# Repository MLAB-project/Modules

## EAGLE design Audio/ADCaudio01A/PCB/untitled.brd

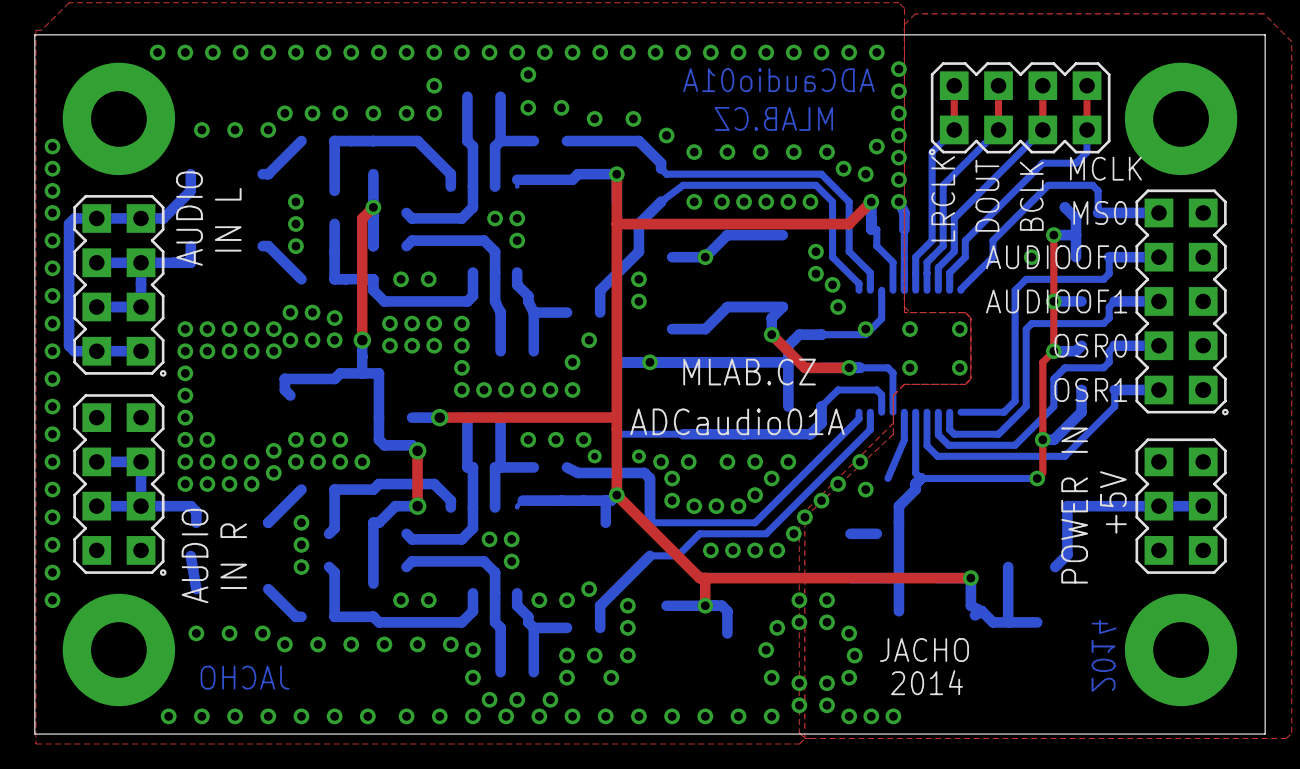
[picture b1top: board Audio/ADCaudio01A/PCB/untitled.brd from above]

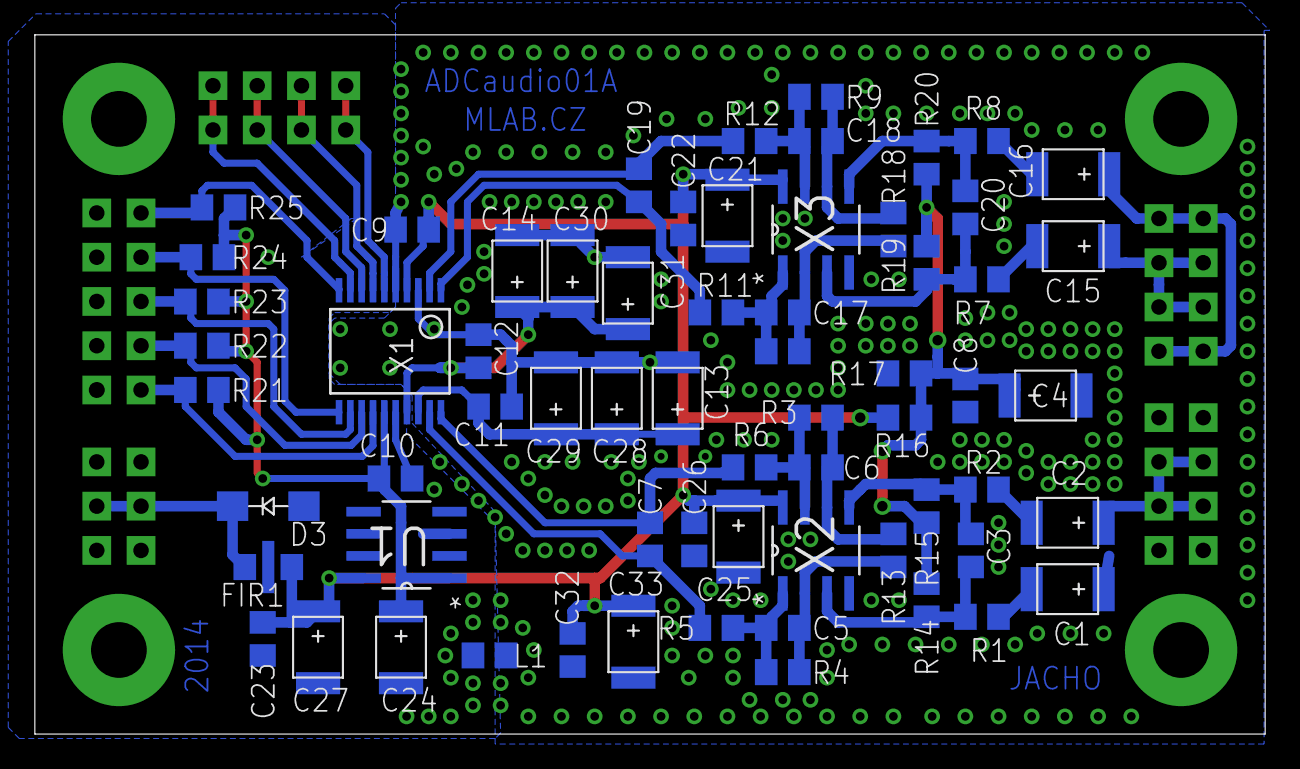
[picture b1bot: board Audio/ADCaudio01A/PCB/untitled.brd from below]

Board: 2 copper layers, 70.6 x 40.1 mm, 74 parts (65 on the bottom side), 39 nets.

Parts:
C1, C2, C4, C13, C14, C15, C16, C24, C28, C29, C30, C31: 10uF; B
C3, C7, C19, C20: 4n7; C0805
C5, C6, C17, C18: 180pF; C0805
C8, C11, C12, C22, C23, C26, C32: 100nF; C0805
C9, C10: 4u7; C0805
C21, C25, C27, C33: 47uF; B
D3: M4; SMA
FIR1: F0805
L1: L0805
R1, R2, R3, R4, R7, R8, R9, R10, R13, R14, R15, R16, R17, R18, R19, R20: 1k; 0805
R5, R6, R11, R12, R21, R22, R23, R24, R25: 22R; 0805
SV1: MA05-2
SV2, SV3, SV5: MA04-2
SV4: MA03-2
U1: LE33CD-TR; SOIC127P600X175-8N
X1: WM8786; SSOP20
X2, X3: LT6231CS; SO8
X4, X5, X6, X7: SROUB3M

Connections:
1: C20.1, R7.2, R19.1, X3.3
4: C3.1, R1.2, R14.1, X2.3
+3.3V: C10.2, C24.+, R21.2, R22.2, R23.2, R24.2, R25.2, U1.1, X1.15
+5V: C9.1, C21.+, C22.1, C23.1, C25.+, C26.1, C27.+, C32.1, C33.+, FIR1.3, R16.2, U1.8, X1.4, X2.8, X3.8
AGND: C1.+, C4.-, C8.2, C9.2, C11.1, C12.1, C13.-, C14.-, C16.+, C21.-, C22.2, C25.-, C26.2, C28.-, C29.-, C30.-, C31.-, C32.2, C33.-, L1.2, R17.1, SV3.1, SV3.2, SV3.7, SV3.8, SV5.1, SV5.2, SV5.7, SV5.8, X1.3, X1.5, X2.4, X3.4
AUDIOOF0: R24.1, SV1.8, X1.11
AUDIOOF1: R23.1, SV1.6, X1.12
AVDD/2: C4.+, C8.1, R14.2, R15.2, R16.1, R17.2, R19.2, R20.2
BCLK: SV2.5, SV2.6, X1.8
DGND: C10.1, C23.2, C24.-, C27.-, D3.A, FIR1.2, L1.1, SV1.1, SV1.3, SV1.5, SV1.7, SV1.9, SV4.1, SV4.2, SV4.5, SV4.6, U1.2, U1.3, U1.5, U1.6, U1.7, X1.16, X6.P$1, X7.P$1
DOUT: SV2.3, SV2.4, X1.7
LRCLK: SV2.1, SV2.2, X1.6
MCLK: SV2.7, SV2.8, X1.9
MS0: R25.1, SV1.10, X1.10
unnamed: C5.2, R4.1, R13.2, X2.2
unnamed: C1.-, R1.1
unnamed: C6.2, R3.1, R13.1, X2.6
unnamed: C2.-, R2.1
unnamed: C6.1, R3.2, R6.1, X2.7
unnamed: C7.1, R5.2, X1.19
unnamed: C17.2, R10.1, R18.2, X3.2
unnamed: C15.-, R7.1
unnamed: C18.2, R9.1, R18.1, X3.6
unnamed: C16.-, R8.1
unnamed: C18.1, R9.2, R12.1, X3.7
unnamed: C19.1, R11.2, X1.1
unnamed: C15.+, SV5.3, SV5.4, SV5.5, SV5.6
unnamed: C20.2, R8.2, R20.1, X3.5
unnamed: C2.+, SV3.3, SV3.4, SV3.5, SV3.6
unnamed: C19.2, R12.2, X1.2
unnamed: C12.2, C14.+, C30.+, C31.+, X1.17
unnamed: C11.2, C13.+, C28.+, C29.+, X1.18
unnamed: C3.2, R2.2, R15.1, X2.5
unnamed: C5.1, R4.2, R5.1, X2.1
unnamed: C17.1, R10.2, R11.1, X3.1
unnamed: C7.2, R6.2, X1.20
unnamed: D3.K, FIR1.1, SV4.3, SV4.4
OSR0: R22.1, SV1.4, X1.13
OSR1: R21.1, SV1.2, X1.14

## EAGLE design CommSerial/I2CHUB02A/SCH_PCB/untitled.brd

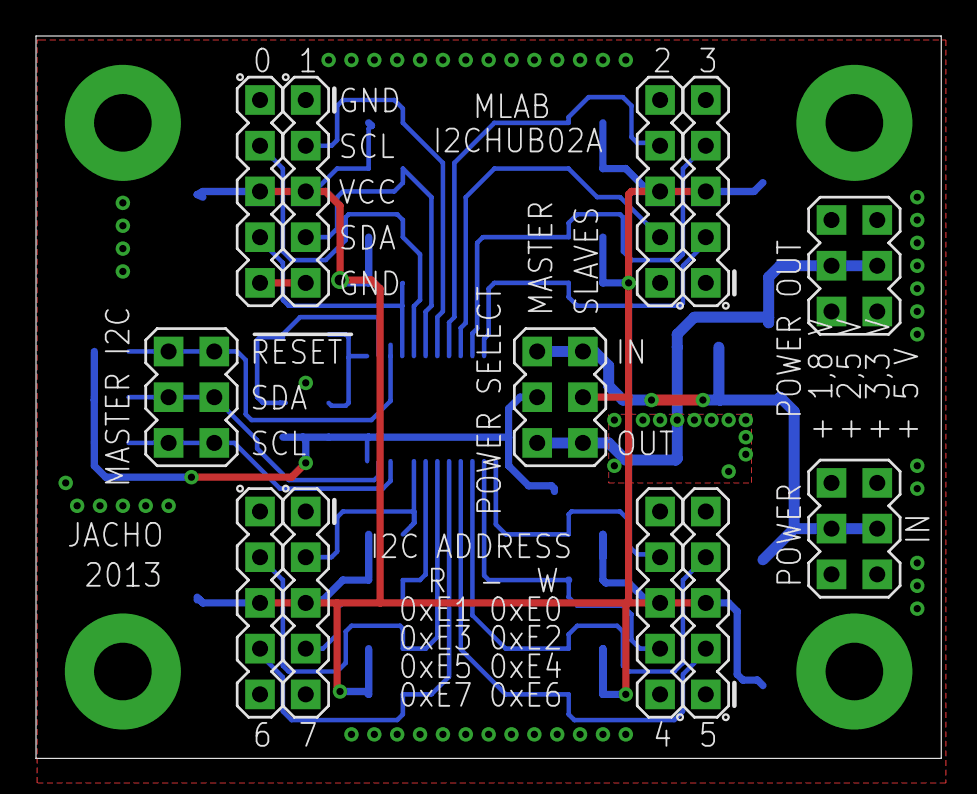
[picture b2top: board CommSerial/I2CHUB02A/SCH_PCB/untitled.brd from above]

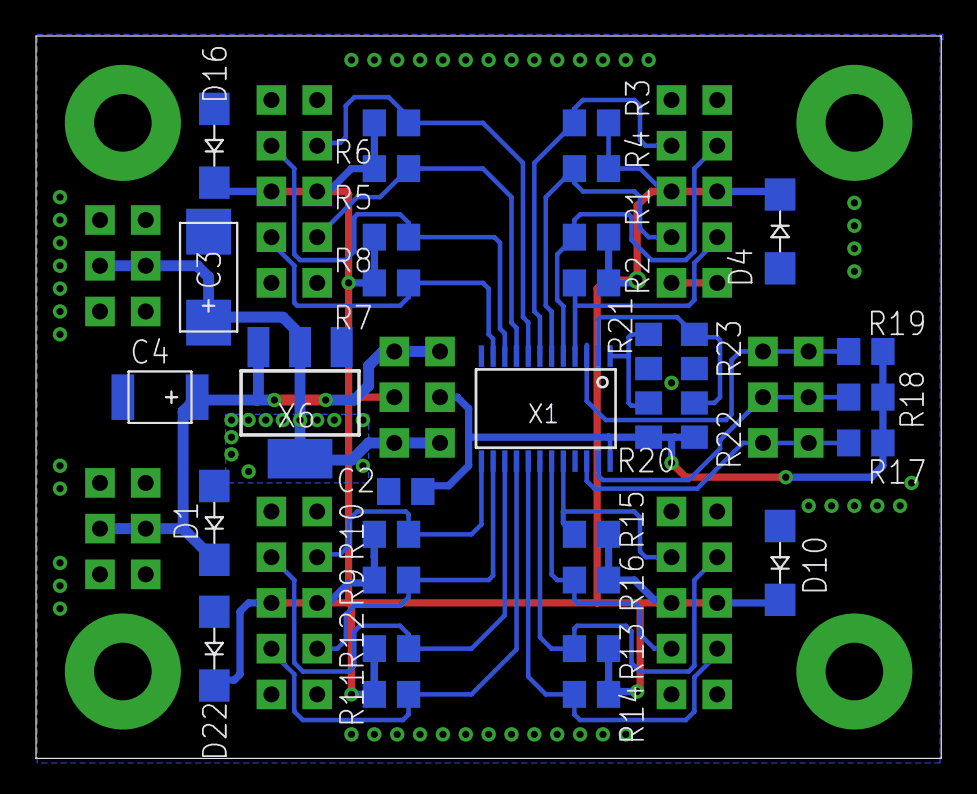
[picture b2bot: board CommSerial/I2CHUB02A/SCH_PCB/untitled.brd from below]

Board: 2 copper layers, 50.3 x 40.1 mm, 49 parts (33 on the bottom side), 26 nets.

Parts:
C2: 100nF; C0805
C3: 47uF; C
C4: 10uF; B
D1: SMA
D4, D10, D16, D22: TRANSIL; SMA
R1, R2, R17, R18, R19: 4k7; 0805
R3, R4, R5, R6, R7, R8, R9, R10, R11, R12, R13, R14, R15, R16: 0805
R20, R21, R22, R23: 0R; 0805
SV1, SV2, SV3, SV4, SV5, SV6, SV7, SV8: MA05-1
SV9, SV10, SV11: MA03-2
SW1: MA03-2
X1: TSS0P24
X2, X3, X4, X5: SROUB3M
X6: LM1117-3.3; SOT223

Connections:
+3.3V: C3.+, SV11.3, SV11.4, SW1.5, SW1.6, X6.2, X6.4
+V1: D4.K, D10.K, D16.K, D22.K, R1.2, R2.2, R3.2, R4.2, R5.2, R6.2, R7.2, R8.2, R9.2, R10.2, R11.2, R12.2, R13.2, R14.2, R15.2, R16.2, SV1.3, SV2.3, SV3.3, SV4.3, SV5.3, SV6.3, SV7.3, SV8.3, SW1.4
+VCC: C4.+, D1.K, SV10.3, SV10.4, SW1.1, SW1.2, X6.3
/RESET: R19.1, SV9.5, SV9.6, X1.3
GND: C2.2, C3.-, C4.-, D1.A, D4.A, D10.A, D16.A, D22.A, R21.1, R23.1, SV1.1, SV1.5, SV2.1, SV2.5, SV3.1, SV3.5, SV4.1, SV4.5, SV5.1, SV5.5, SV6.1, SV6.5, SV7.1, SV7.5, SV8.1, SV8.5, SV10.1, SV10.2, SV10.5, SV10.6, SV11.1, SV11.2, SV11.5, SV11.6, X1.12, X1.21, X2.P$1, X3.P$1, X4.P$1, X5.P$1, X6.1
unnamed: C2.1, R17.2, R18.2, R19.2, R20.2, R22.2, SW1.3, X1.24
unnamed: R20.1, R21.2, X1.1
unnamed: R22.1, R23.2, X1.2
SC0: R1.1, SV1.2, X1.5
SC1: R3.1, SV2.2, X1.7
SC2: R5.1, SV3.2, X1.9
SC3: R7.1, SV4.2, X1.11
SC4: R9.1, SV5.2, X1.14
SC5: R11.1, SV6.2, X1.16
SC6: R13.1, SV7.2, X1.18
SC7: R15.1, SV8.2, X1.20
SCL: R17.1, SV9.1, SV9.2, X1.22
SD0: R2.1, SV1.4, X1.4
SD1: R4.1, SV2.4, X1.6
SD2: R6.1, SV3.4, X1.8
SD3: R8.1, SV4.4, X1.10
SD4: R10.1, SV5.4, X1.13
SD5: R12.1, SV6.4, X1.15
SD6: R14.1, SV7.4, X1.17
SD7: R16.1, SV8.4, X1.19
SDA: R18.1, SV9.3, SV9.4, X1.23

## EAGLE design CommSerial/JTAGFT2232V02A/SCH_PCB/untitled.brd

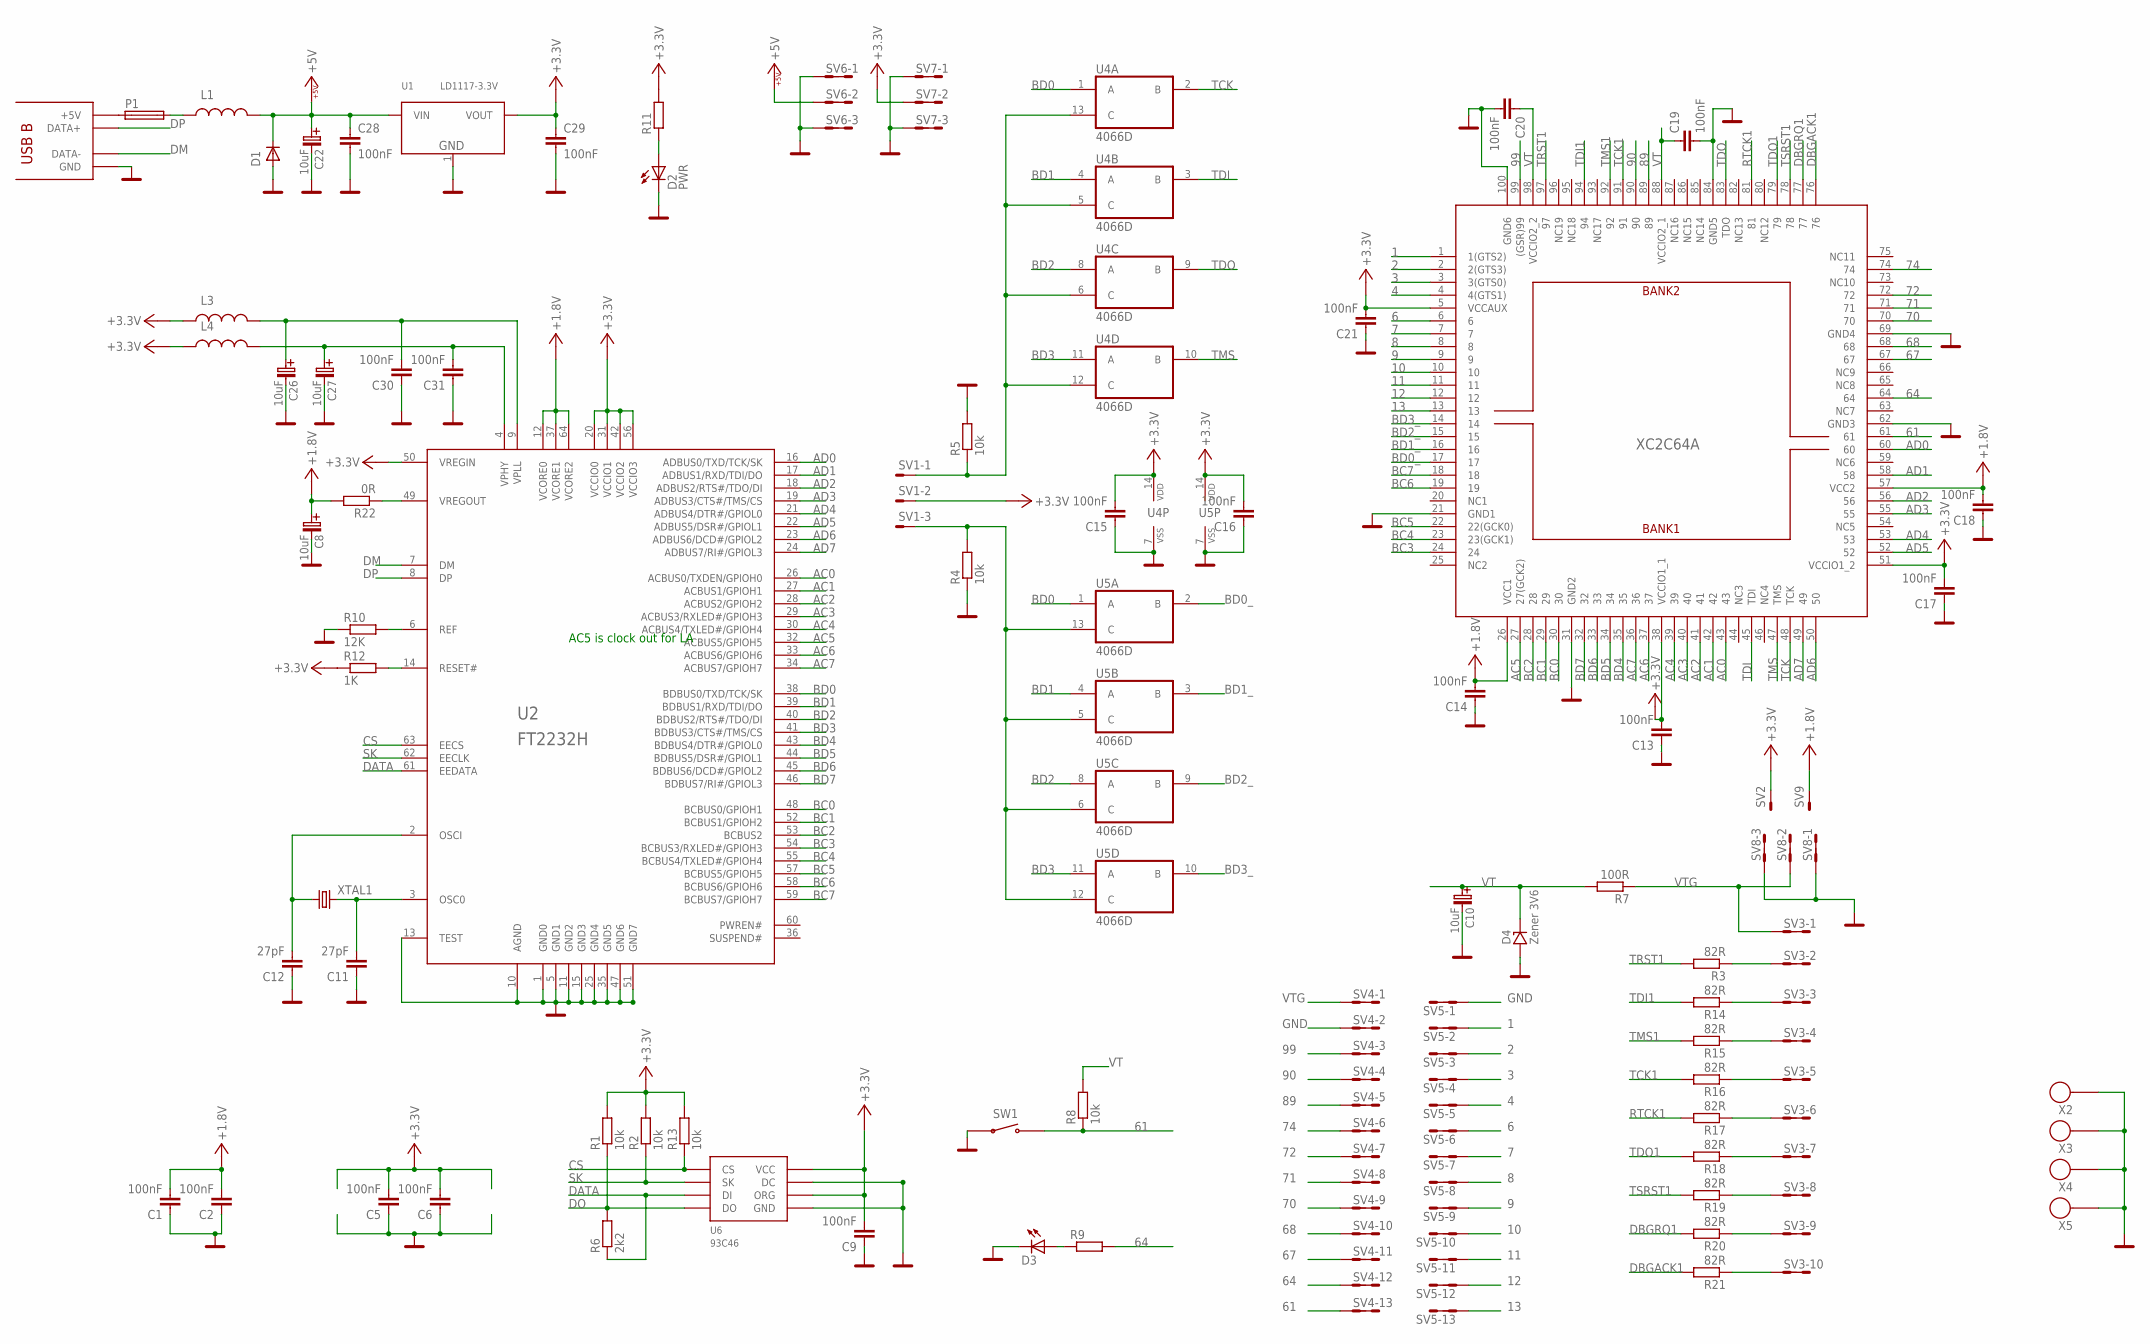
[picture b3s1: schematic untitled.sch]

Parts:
C1, C2, C5, C6, C9, C13, C14, C15, C16, C17, C18, C19, C20, C21, C28, C29, C30, C31: 100nF; C0805
C8, C10, C22, C26, C27: 10uF; B
C11, C12: 27pF; C0805
D1: D-OB.SMA; SMA
D2: PWR; 1206
D3: LED1206; 1206
D4: Zener 3V6; MINIMELF
L1: L0805
L3, L4: L1210; 1210
P1: POJISTKA_1812; 1812
R1, R2, R4, R5, R8, R13: 10k; 0805
R3, R14, R15, R16, R17, R18, R19, R20, R21: 82R; 0805
R6: 2k2; 0805
R7: 100R; 0805
R9, R11: R0805; 0805
R10: 12K; 0805
R12: 1K; 0805
R22: 0R; 0805
SV1: MA03-1
SV2, SV9: MA01-1
SV3: MA10-2
SV4, SV5: MA13-2
SV6, SV7, SV8: MA03-2
SW1: TACT-64K
U1: LD1117-3.3V; SOT223
U2: FT2232H; LQFP64
U3: XC2C64A; VQ100
U4, U5: 4066D; SO14
U6: 93C46; SOIC8
X1: USB_B
X2, X3, X4, X5: SROUB3M
XTAL1: KRYSLAL_S49; S49

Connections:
1: SV5.3, SV5.4, U3.1 (1(GTS2))
2: SV5.5, SV5.6, U3.2 (2(GTS3))
3: SV5.7, SV5.8, U3.3 (3(GTS0))
4: SV5.9, SV5.10, U3.4 (4(GTS1))
6: SV5.11, SV5.12, U3.6
7: SV5.13, SV5.14, U3.7
8: SV5.15, SV5.16, U3.8
9: SV5.17, SV5.18, U3.9
10: SV5.19, SV5.20, U3.10
11: SV5.21, SV5.22, U3.11
12: SV5.23, SV5.24, U3.12
13: SV5.25, SV5.26, U3.13
61: R8.1, SV4.25, SV4.26, SW1.P$3, SW1.P$4, U3.61
64: R9.2, SV4.23, SV4.24, U3.64
67: SV4.21, SV4.22, U3.67
68: SV4.19, SV4.20, U3.68
70: SV4.17, SV4.18, U3.70
71: SV4.15, SV4.16, U3.71
72: SV4.13, SV4.14, U3.72
74: SV4.11, SV4.12, U3.74
89: SV4.9, SV4.10, U3.89
90: SV4.7, SV4.8, U3.90
99: SV4.5, SV4.6, U3.99 ((GSR)99)
+1.8V: C1.2, C2.2, C8.+ (C_EL+), C14.2, C18.2, R22.2, SV9.1, U2.12 (VCORE0), U2.37 (VCORE1), U2.64 (VCORE2), U3.26 (VCC1), U3.57 (VCC2)
+3.3V: C5.2, C6.2, C9.2, C13.2, C15.2, C16.2, C17.2, C21.2, C29.1, L3.P$1 (1), L4.P$1 (1), R1.2, R2.2, R11.2, R12.1, R13.2, SV1.2, SV2.1, SV7.3, SV7.4, U1.2 (VOUT), U2.20 (VCCIO0), U2.31 (VCCIO1), U2.42 (VCCIO2), U2.50 (VREGIN), U2.56 (VCCIO3), U3.5 (VCCAUX), U3.38 (VCCIO1_1), U3.51 (VCCIO1_2), U4.14 (VDD), U5.14 (VDD), U6.6 (ORG), U6.8 (VCC)
+5V: C22.+ (C_EL+), C28.1, D1.K (C), L1.2, SV6.3, SV6.4, U1.3 (VIN)
AC0: U2.26 (ACBUS0/TXDEN/GPIOH0), U3.43
AC1: U2.27 (ACBUS1/GPIOH1), U3.42
AC2: U2.28 (ACBUS2/GPIOH2), U3.41
AC3: U2.29 (ACBUS3/RXLED#/GPIOH3), U3.40
AC4: U2.30 (ACBUS4/TXLED#/GPIOH4), U3.39
AC5: U2.32 (ACBUS5/GPIOH5), U3.27 (27(GCK2))
AC6: U2.33 (ACBUS6/GPIOH6), U3.37
AC7: U2.34 (ACBUS7/GPIOH7), U3.36
AD0: U2.16 (ADBUS0/TXD/TCK/SK), U3.60
AD1: U2.17 (ADBUS1/RXD/TDI/DO), U3.58
AD2: U2.18 (ADBUS2/RTS#/TDO/DI), U3.56
AD3: U2.19 (ADBUS3/CTS#/TMS/CS), U3.55
AD4: U2.21 (ADBUS4/DTR#/GPIOL0), U3.53
AD5: U2.22 (ADBUS5/DSR#/GPIOL1), U3.52
AD6: U2.23 (ADBUS6/DCD#/GPIOL2), U3.50
AD7: U2.24 (ADBUS7/RI#/GPIOL3), U3.49
BC0: U2.48 (BCBUS0/GPIOH1), U3.30
BC1: U2.52 (BCBUS1/GPIOH2), U3.29
BC2: U2.53 (BCBUS2), U3.28
BC3: U2.54 (BCBUS3/RXLED#/GPIOH3), U3.24
BC4: U2.55 (BCBUS4/TXLED#/GPIOH4), U3.23 (23(GCK1))
BC5: U2.57 (BCBUS5/GPIOH5), U3.22 (22(GCK0))
BC6: U2.58 (BCBUS6/GPIOH6), U3.19
BC7: U2.59 (BCBUS7/GPIOH7), U3.18
BD0: U2.38 (BDBUS0/TXD/TCK/SK), U4.1 (A), U5.1 (A)
BD0_: U3.17, U5.2 (B)
BD1: U2.39 (BDBUS1/RXD/TDI/DO), U4.4 (A), U5.4 (A)
BD1_: U3.16, U5.3 (B)
BD2: U2.40 (BDBUS2/RTS#/TDO/DI), U4.8 (A), U5.8 (A)
BD2_: U3.15, U5.9 (B)
BD3: U2.41 (BDBUS3/CTS#/TMS/CS), U4.11 (A), U5.11 (A)
BD3_: U3.14, U5.10 (B)
BD4: U2.43 (BDBUS4/DTR#/GPIOL0), U3.35
BD5: U2.44 (BDBUS5/DSR#/GPIOL1), U3.34
BD6: U2.45 (BDBUS6/DCD#/GPIOL2), U3.33
BD7: U2.46 (BDBUS7/RI#/GPIOL3), U3.32
CS: R13.1, U2.63 (EECS), U6.1 (CS)
DATA: R6.1, U2.61 (EEDATA), U6.3 (DI)
DBGACK1: R21.2, U3.76
DBGRQ1: R20.2, U3.77
DM: U2.7 (DM), X1.2 (DATA-)
DO: R1.1, R6.2, U6.4 (DO)
DP: U2.8 (DP), X1.3 (DATA+)
GND: C1.1, C2.1, C5.1, C6.1, C8.- (C_EL-), C9.1, C10.- (C_EL-), C11.1, C12.1, C13.1, C14.1, C15.1, C16.1, C17.1, C18.1, C19.2, C20.2, C21.1, C22.- (C_EL-), C26.- (C_EL-), C27.- (C_EL-), C28.2, C29.2, C30.1, C31.1, D1.A, D2.K (C), D3.K (C), D4.A, R4.1, R5.2, R10.1, SV4.3, SV4.4, SV5.1, SV5.2, SV6.1, SV6.2, SV6.5, SV6.6, SV7.1, SV7.2, SV7.5, SV7.6, SV8.1, SV8.2, SV8.5, SV8.6, SW1.P$1, SW1.P$2, U1.1 (GND), U2.1 (GND0), U2.5 (GND1), U2.10 (AGND), U2.11 (GND2), U2.13 (TEST), U2.15 (GND3), U2.25 (GND4), U2.35 (GND5), U2.47 (GND6), U2.51 (GND7), U3.21 (GND1), U3.31 (GND2), U3.62 (GND3), U3.69 (GND4), U3.84 (GND5), U3.100 (GND6), U4.7 (VSS), U5.7 (VSS), U6.5 (GND), U6.7 (DC), X1.4 (GND), X1.GND, X1.GND2 (GND), X2.P$1, X3.P$1, X4.P$1, X5.P$1
unnamed: C11.2, U2.3 (OSC0), XTAL1.P$2 (2)
unnamed: C12.2, U2.2 (OSCI), XTAL1.P$1 (1)
unnamed: R10.2, U2.6 (REF)
unnamed: R12.2, U2.14 (RESET#)
unnamed: R3.1, SV3.3, SV3.4
unnamed: D3.A, R9.1
unnamed: D2.A, R11.1
unnamed: P1.1, X1.1 (+5V)
unnamed: L1.1, P1.2
unnamed: R14.1, SV3.5, SV3.6
unnamed: R15.1, SV3.7, SV3.8
unnamed: R16.1, SV3.9, SV3.10
unnamed: R17.1, SV3.11, SV3.12
unnamed: R18.1, SV3.13, SV3.14
unnamed: R19.1, SV3.15, SV3.16
unnamed: R20.1, SV3.17, SV3.18
unnamed: R21.1, SV3.19, SV3.20
unnamed: R22.1, U2.49 (VREGOUT)
unnamed: R5.1, SV1.1, U4.5 (C), U4.6 (C), U4.12 (C), U4.13 (C)
unnamed: R4.2, SV1.3, U5.5 (C), U5.6 (C), U5.12 (C), U5.13 (C)
RTCK1: R17.2, U3.81
SK: R2.1, U2.62 (EECLK), U6.2 (SK)
TCK: U3.48 (TCK), U4.2 (B)
TCK1: R16.2, U3.91
TDI: U3.45 (TDI), U4.3 (B)
TDI1: R14.2, U3.94
TDO: U3.83 (TDO), U4.9 (B)
TDO1: R18.2, U3.79
TMS: U3.47 (TMS), U4.10 (B)
TMS1: R15.2, U3.92
TRST1: R3.2, U3.97
TSRST1: R19.2, U3.78
VPHY: C27.+ (C_EL+), C31.2, L4.P$2 (2), U2.4 (VPHY)
VPLL: C26.+ (C_EL+), C30.2, L3.P$2 (2), U2.9 (VPLL)
VT: C10.+ (C_EL+), C19.1, C20.1, D4.C (K), R7.2, R8.2, U3.88 (VCCIO2_1), U3.98 (VCCIO2_2)
VTG: R7.1, SV3.1, SV3.2, SV4.1, SV4.2, SV8.3, SV8.4

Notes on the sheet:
AC5 is clock out for LA
XC2C64A

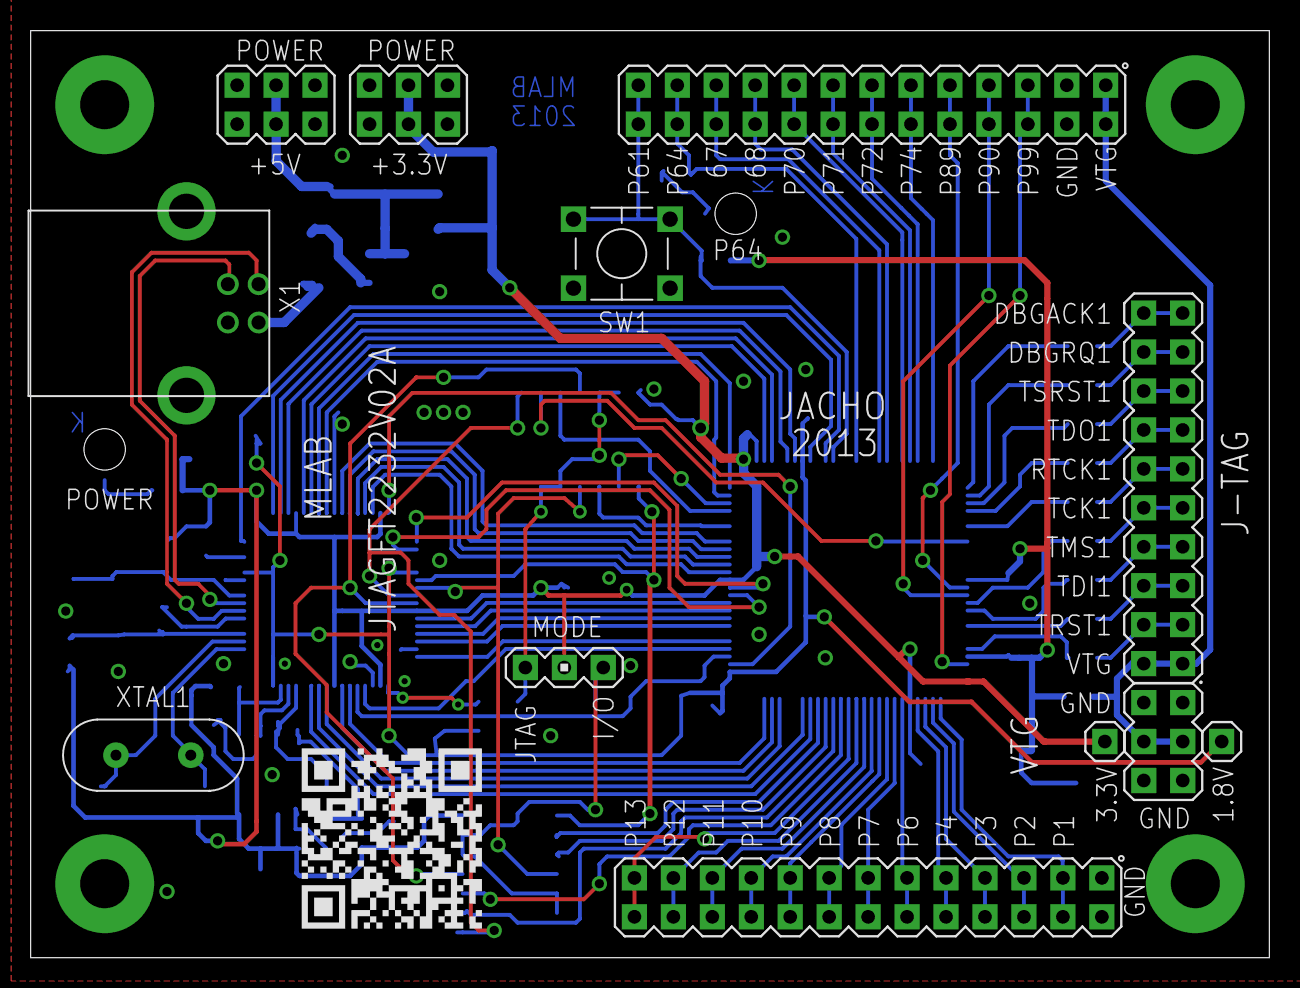
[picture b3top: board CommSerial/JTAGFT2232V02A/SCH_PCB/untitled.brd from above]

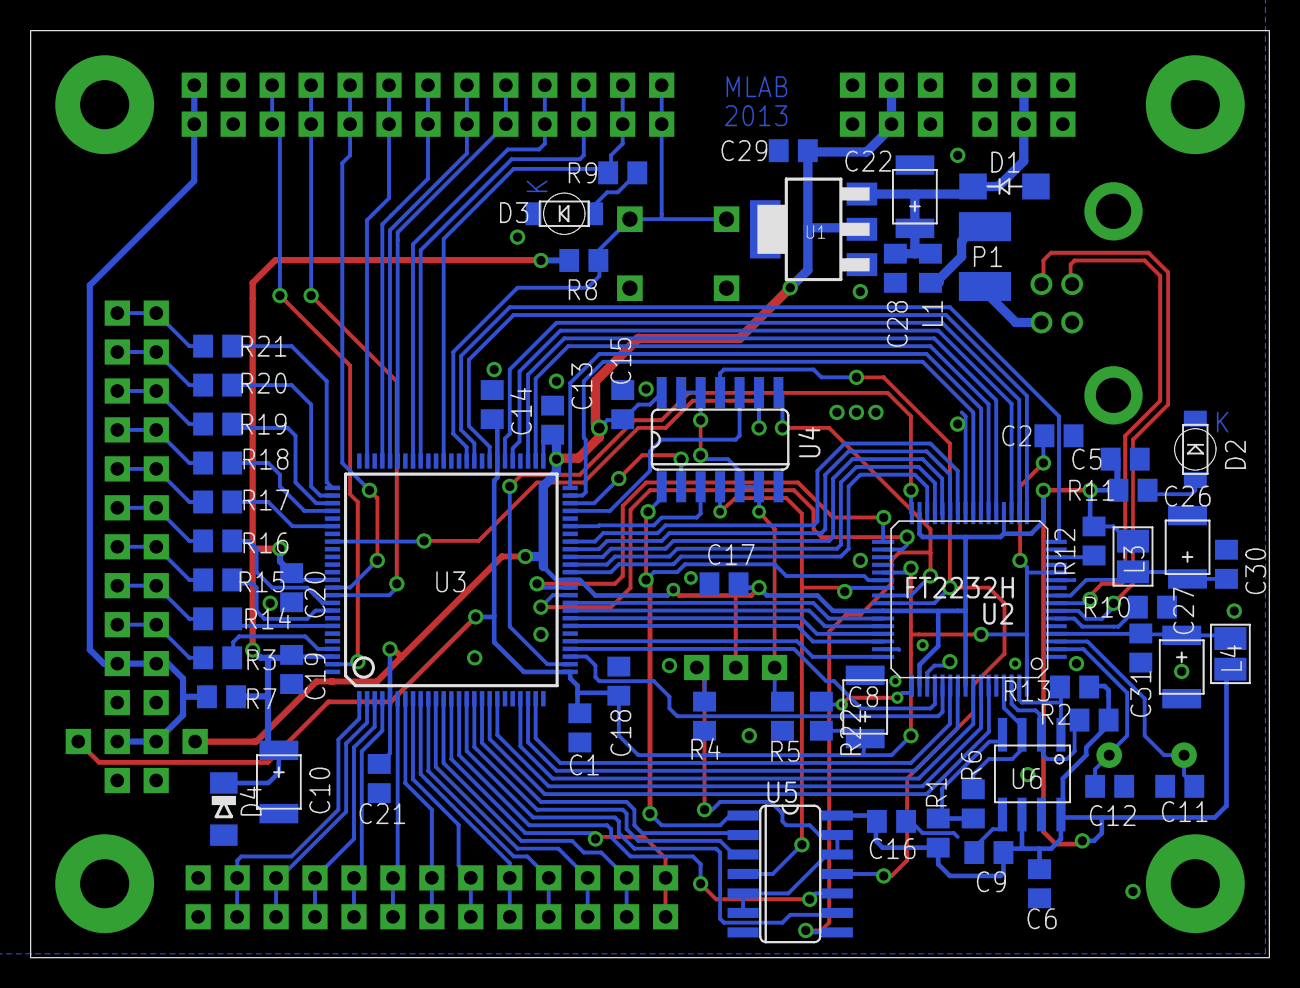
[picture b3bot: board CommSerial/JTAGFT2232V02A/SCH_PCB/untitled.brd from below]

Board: 2 copper layers, 80.8 x 60.5 mm, 77 parts (61 on the bottom side), 106 nets.

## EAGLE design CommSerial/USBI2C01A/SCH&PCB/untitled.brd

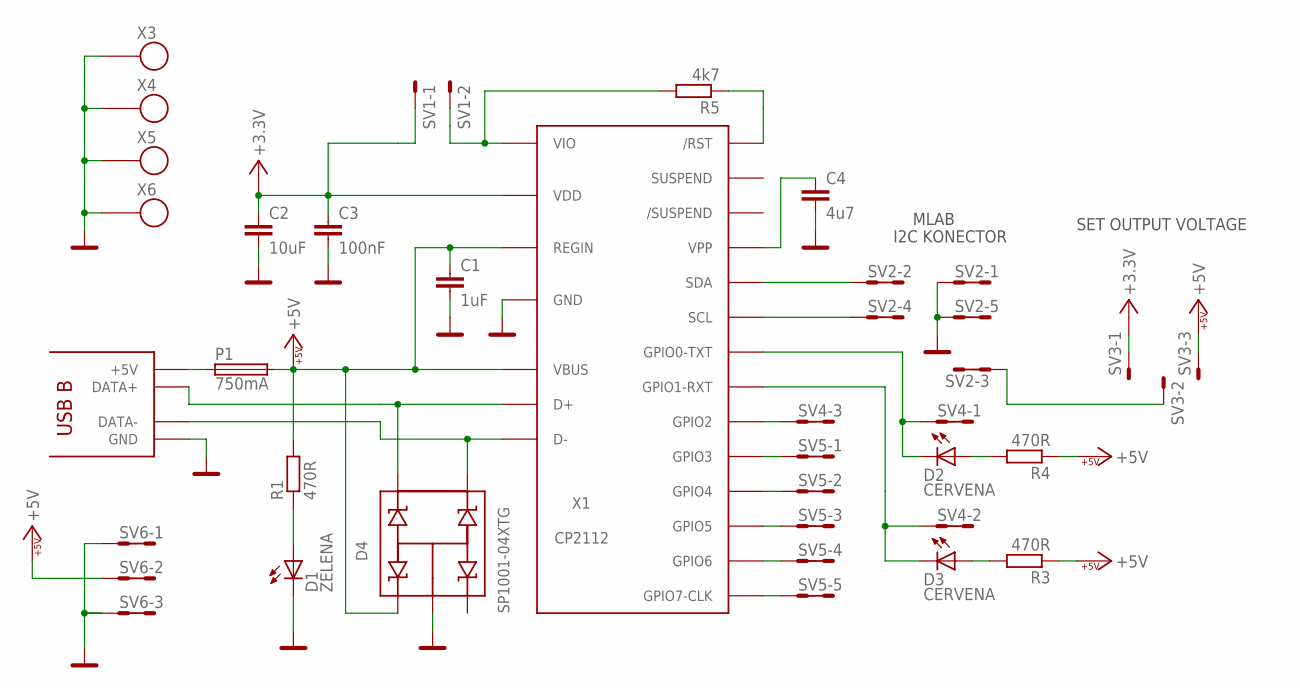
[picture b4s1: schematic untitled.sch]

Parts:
C1: 1uF; C0805
C2: 10uF; C0805
C3: 100nF; C0805
C4: 4u7; C0805
D1: ZELENA; 1206_2
D2, D3: CERVENA; 1206_2
D4: SP1001-04XTG; SOT553
P1: 750mA; 1812
R1, R3, R4: 470R; 0805
R5: 4k7; 0805
SV1: MA02-1
SV2, SV5: MA05-2
SV3: MA03-1
SV4, SV6: MA03-2
X1: CP2112; QFN-24
X2: USB_B
X3, X4, X5, X6: SROUB3M

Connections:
0: D2.K (C), SV4.1, SV4.2, X1.P$23 (GPIO0-TXT)
1: D3.K (C), SV4.3, SV4.4, X1.P$22 (GPIO1-RXT)
2: SV4.5, SV4.6, X1.P$21 (GPIO2)
3: SV5.1, SV5.2, X1.P$20 (GPIO3)
4: SV5.3, SV5.4, X1.P$15 (GPIO4)
5: SV5.5, SV5.6, X1.P$14 (GPIO5)
6: SV5.7, SV5.8, X1.P$13 (GPIO6)
7: SV5.9, SV5.10, X1.P$12 (GPIO7-CLK)
GND: C1.2, C2.2, C3.2, C4.2, D1.K (C), D4.2, SV2.1, SV2.2, SV2.9, SV2.10, SV6.1, SV6.2, SV6.5, SV6.6, X1.P$2 (GND), X1.P$25 (GND), X2.4 (GND), X2.GND, X2.GND2 (GND), X3.P$1, X4.P$1, X5.P$1, X6.P$1
unnamed: D4.5, X1.P$3 (D+), X2.3 (DATA+)
unnamed: D4.4, X1.P$4 (D-), X2.2 (DATA-)
unnamed: C4.1, X1.P$16 (VPP)
unnamed 12: X1.P$17 (/SUSPEND); also elsewhere on the board
unnamed: P1.1, X2.1 (+5V)
unnamed: D1.A, R1.1
unnamed: R5.2, SV1.2, X1.P$5 (VIO)
unnamed: D3.A, R3.2
unnamed: SV2.5, SV2.6, SV3.2
unnamed: D2.A, R4.2
unnamed: R5.1, X1.P$9 (/RST)
SCL: SV2.7, SV2.8, X1.P$24 (SCL)
SDA: SV2.3, SV2.4, X1.P$1 (SDA)

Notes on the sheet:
SET OUTPUT VOLTAGE
I2C KONECTOR
MLAB

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
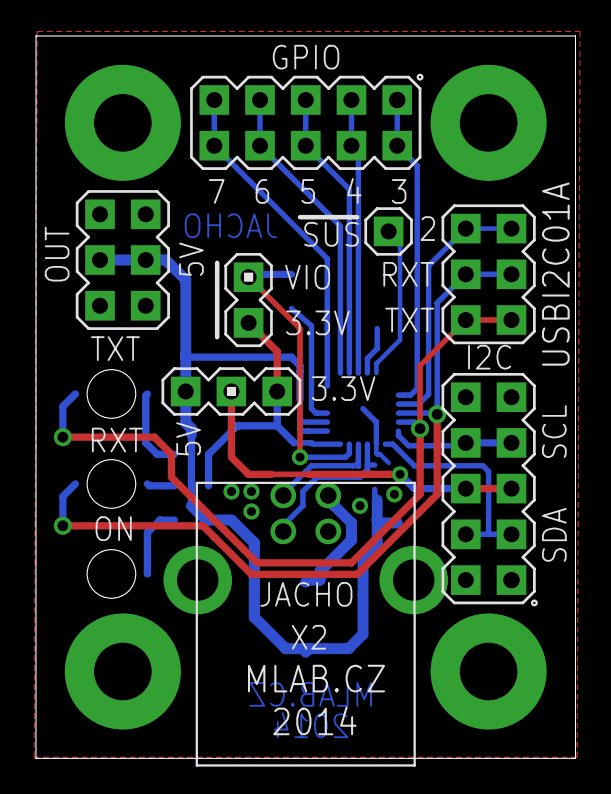
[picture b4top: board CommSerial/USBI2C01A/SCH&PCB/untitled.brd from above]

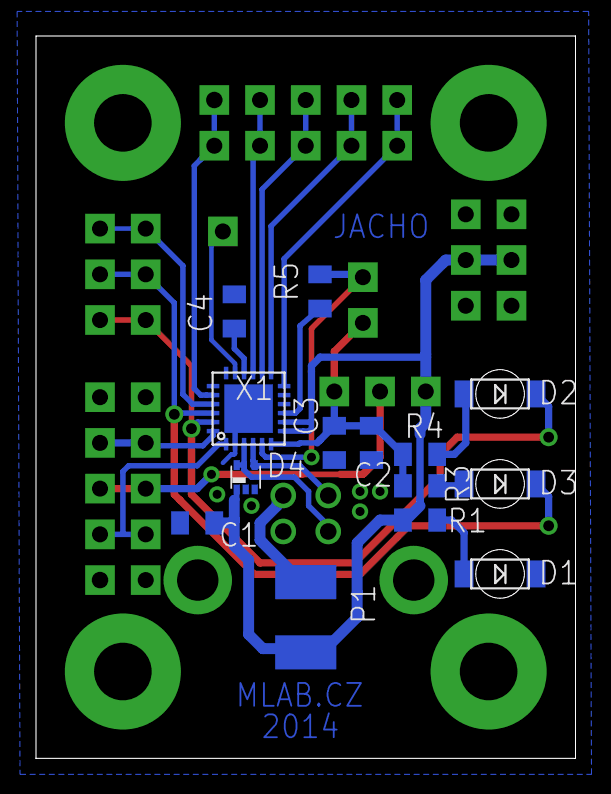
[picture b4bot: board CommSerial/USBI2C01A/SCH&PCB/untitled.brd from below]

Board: 2 copper layers, 30.0 x 40.1 mm, 26 parts (14 on the bottom side), 24 nets.

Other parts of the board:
SV7: MA01-1

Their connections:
unnamed 12: SV7.1; also elsewhere on the board

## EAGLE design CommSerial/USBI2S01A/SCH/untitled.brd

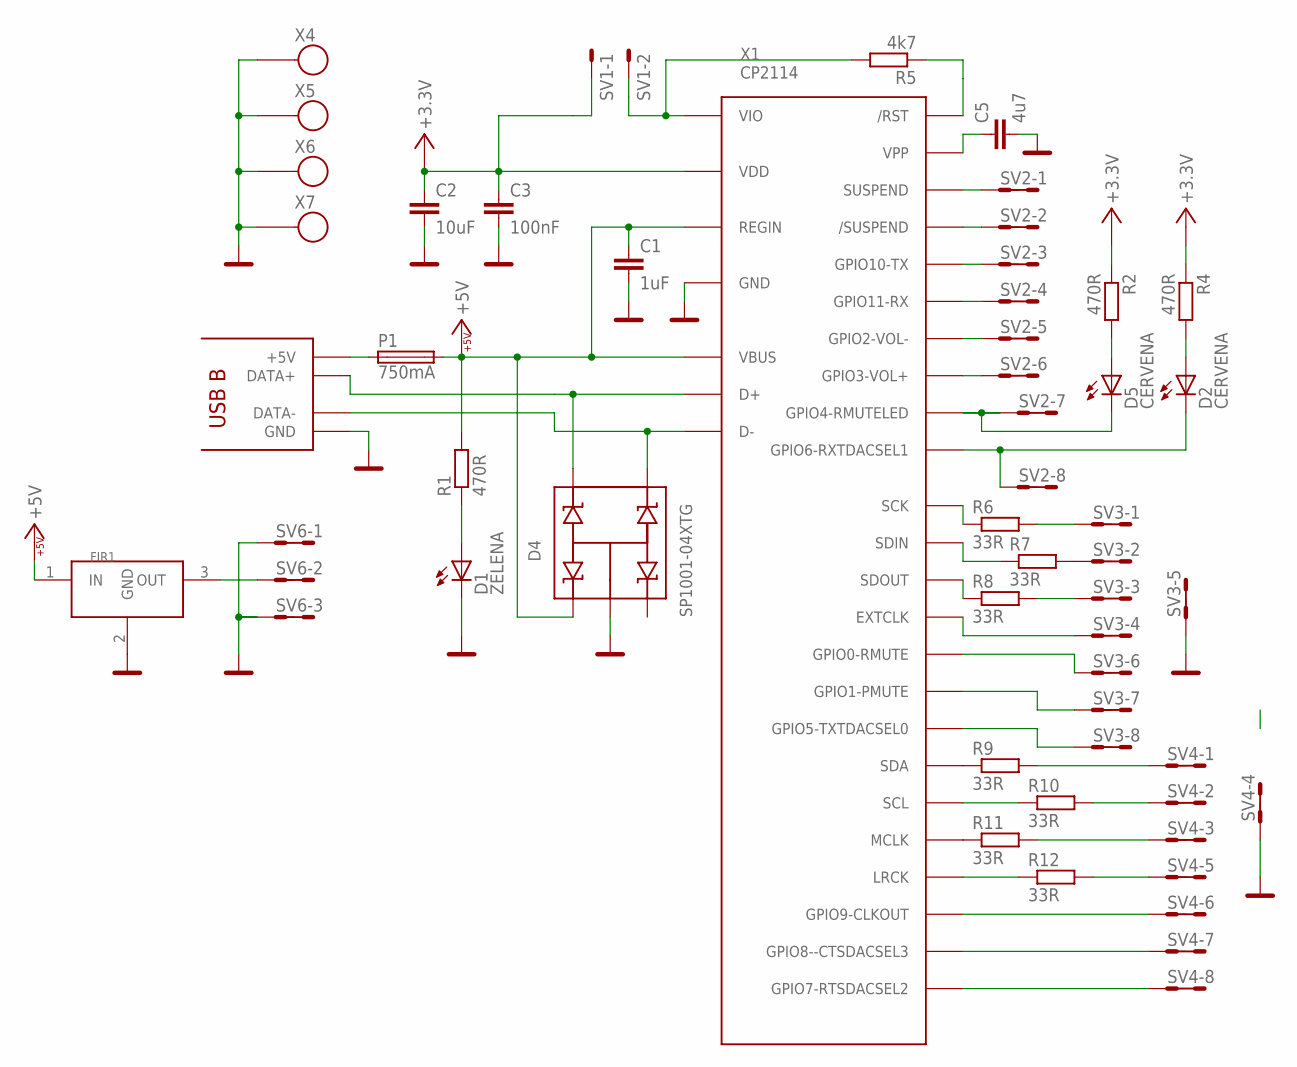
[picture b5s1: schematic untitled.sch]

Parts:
C1: 1uF; C0805
C2: 10uF; C0805
C3: 100nF; C0805
C5: 4u7; C0805
D1: ZELENA; 1206_2
D2, D5: CERVENA; 1206_2
D4: SP1001-04XTG; SOT553
FIR1: FILTR0805; F0805
P1: 750mA; 1812
R1, R2, R4: 470R; 0805
R5: 4k7; 0805
R6, R7, R8, R9, R10, R11, R12: 33R; 0805
SV1: MA02-1
SV2, SV3, SV4: MA08-2
SV6: MA03-2
X1: CP2114; QFN-32
X3: USB_B
X4, X5, X6, X7: SROUB3M

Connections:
+3.3V: C2.1, C3.1, R2.1, R4.1, SV1.1, X1.7 (VDD)
+5V: C1.1, D4.1, FIR1.1 (IN), P1.2, R1.2, X1.8 (REGIN), X1.9 (VBUS)
/SUSPEND: SV2.3, SV2.4, X1.17 (/SUSPEND)
EXTCLK: SV3.7, SV3.8, X1.31 (EXTCLK)
GND: C1.2, C2.2, C3.2, C5.2, D1.K (C), D4.2, FIR1.2 (GND), SV3.9, SV3.10, SV4.7, SV4.8, SV6.1, SV6.2, SV6.5, SV6.6, X1.3 (GND), X1.EXP (GND), X3.4 (GND), X3.GND, X3.GND2 (GND), X4.P$1, X5.P$1, X6.P$1, X7.P$1
GP0: SV3.11, SV3.12, X1.30 (GPIO0-RMUTE)
GP1: SV3.13, SV3.14, X1.29 (GPIO1-PMUTE)
GP2: SV2.9, SV2.10, X1.14 (GPIO2-VOL-)
GP3: SV2.11, SV2.12, X1.13 (GPIO3-VOL+)
GP4: D5.K (C), SV2.13, SV2.14, X1.12 (GPIO4-RMUTELED)
GP5: SV3.15, SV3.16, X1.28 (GPIO5-TXTDACSEL0)
GP6: D2.K (C), SV2.15, SV2.16, X1.11 (GPIO6-RXTDACSEL1)
GP7: SV4.15, SV4.16, X1.19 (GPIO7-RTSDACSEL2)
GP08: SV4.13, SV4.14, X1.20 (GPIO8--CTSDACSEL3)
GP9: SV4.11, SV4.12, X1.22 (GPIO9-CLKOUT)
GP10: SV2.5, SV2.6, X1.16 (GPIO10-TX)
GP11: SV2.7, SV2.8, X1.15 (GPIO11-RX)
LRCK: R12.2, SV4.9, SV4.10
MCLK: R11.2, SV4.5, SV4.6
unnamed: D4.5, X1.4 (D+), X3.3 (DATA+)
unnamed: D4.4, X1.5 (D-), X3.2 (DATA-)
unnamed: FIR1.3 (OUT), SV6.3, SV6.4
unnamed: C5.1, X1.21 (VPP)
unnamed: P1.1, X3.1 (+5V)
unnamed: D1.A, R1.1
unnamed: D5.A, R2.2
unnamed: D2.A, R4.2
unnamed: R5.1, X1.10 (/RST)
unnamed: R8.1, X1.32 (SDOUT)
unnamed: R7.1, X1.1 (SDIN)
unnamed: R6.1, X1.2 (SCK)
unnamed: R9.1, X1.27 (SDA)
unnamed: R10.1, X1.26 (SCL)
unnamed: R11.1, X1.25 (MCLK)
unnamed: R12.1, X1.23 (LRCK)
SCK: R6.2, SV3.1, SV3.2
SCL: R10.2, SV4.3, SV4.4
SDA: R9.2, SV4.1, SV4.2
SDIN: R7.2, SV3.3, SV3.4
SDOUT: R8.2, SV3.5, SV3.6
SUSPEND: SV2.1, SV2.2, X1.18 (SUSPEND)
VIO: R5.2, SV1.2, X1.6 (VIO)

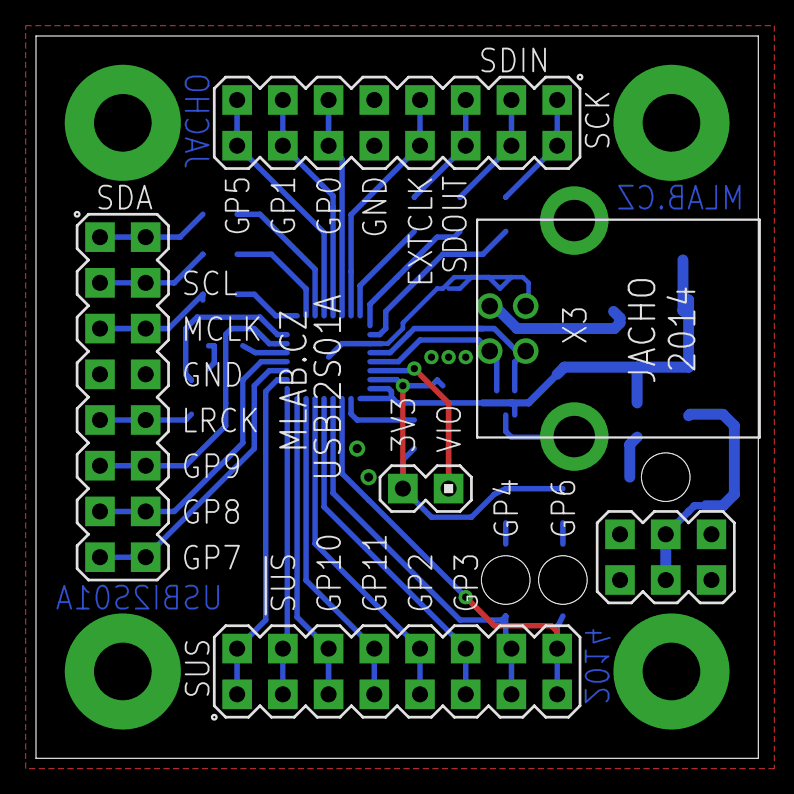
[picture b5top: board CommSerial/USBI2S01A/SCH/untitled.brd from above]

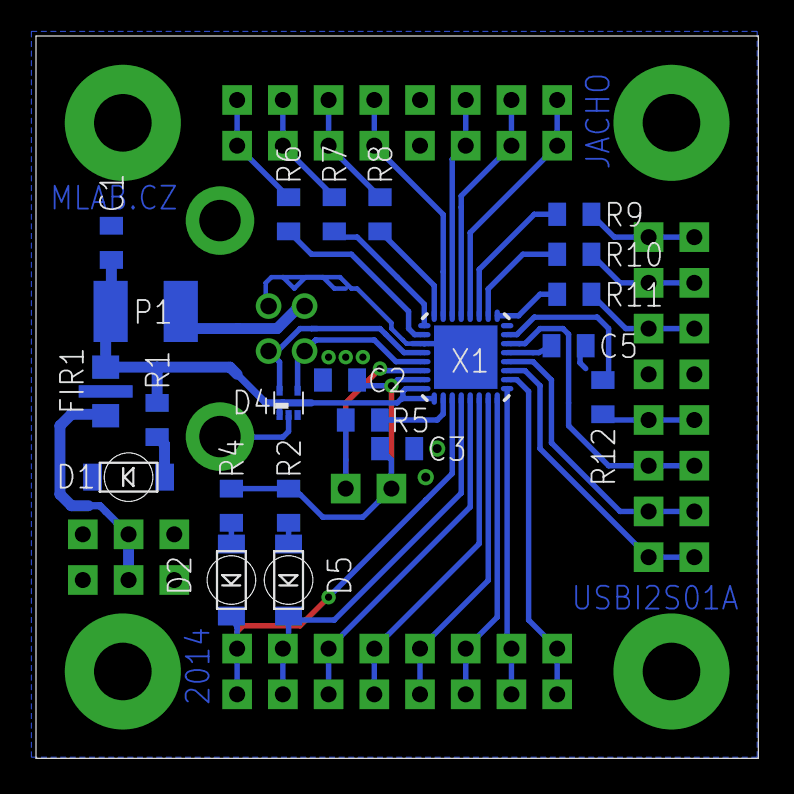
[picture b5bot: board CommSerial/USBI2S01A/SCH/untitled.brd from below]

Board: 2 copper layers, 40.1 x 40.1 mm, 32 parts (22 on the bottom side), 42 nets.
